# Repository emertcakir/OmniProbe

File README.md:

# OmniProbe

**A Universal Open-Source Debugging and Signal Analysis Platform for Embedded Engineers**

OmniProbe is an open-source hardware and firmware platform designed to simplify embedded system development, debugging, and protocol analysis.

Built around the RP2040 microcontroller, OmniProbe combines multiple engineering tools into a single compact device, reducing the need for separate adapters, analyzers, and interface boards.

---

## Why OmniProbe?

Embedded developers often rely on multiple tools for debugging and communication:

* SWD Debug Probe
* USB-to-UART Adapter
* Logic Analyzer
* SPI Debug Tool
* I2C Interface
* GPIO Test Board

OmniProbe aims to bring all of these capabilities into a single open-source platform.

---

## Key Features

### Debugging Interfaces

* SWD Debugging
* JTAG Support
* CMSIS-DAP Compatible Firmware

### Communication Interfaces

* USB to UART Bridge
* SPI Interface
* I2C Interface
* GPIO Access

### Logic Analyzer

* Up to 16 Digital Channels
* RP2040 PIO-Based Sampling Engine
* Planned Sigrok / PulseView Integration

### Multi-Voltage Operation

* 1.8V Support
* 3.3V Support
* 5V Support
* Bidirectional Level Shifting

### Hardware Features

* USB Type-C Connectivity
* ESD Protection
* Polyfuse Protection
* EMI Filtering
* Reverse Polarity Protection

---

## Hardware Architecture

The hardware architecture is divided into several independent modules:

* Power Management
* USB Type-C Interface
* RP2040 Core
* QSPI Flash Memory
* Level Shifting Subsystem
* Debug Interfaces
* Logic Analyzer Engine
* Protection Layer

This modular architecture allows future expansion without redesigning the entire system.

---

## Project Goals

* Open-Source Hardware
* Open-Source Firmware
* Professional Development Tool
* Affordable Manufacturing Cost
* Maker-Friendly Design
* Educational Value
* Extensible Architecture

---

## Repository Structure

```text
OmniProbe/
├── docs/
├── hardware/
├── firmware/
├── software/
├── tests/
└── assets/
```

---

## Current Status

Project Phase: System Architecture & Hardware Design

OmniProbe is currently in the hardware architecture and schematic design phase. The project is being developed as a fully open-source platform, including hardware design files, documentation, and firmware sources.

The first release focuses on establishing a reliable and extensible foundation for debugging, protocol analysis, and embedded development workflows.

Future updates will expand functionality, improve performance, and introduce additional protocol support while maintaining compatibility with the existing hardware platform.
---

## Open Hardware

All design files, schematics, PCB layouts, BOMs, and firmware sources will be publicly available.

The objective of OmniProbe is not only to provide a useful engineering tool, but also to serve as a learning resource for hardware and embedded system developers.

---

## Contributing

Contributions, design reviews, bug reports, feature requests, and pull requests are welcome.

---

## License

MIT License

---

## Disclaimer

OmniProbe is currently under active development. Hardware and firmware specifications may change before the first stable release.

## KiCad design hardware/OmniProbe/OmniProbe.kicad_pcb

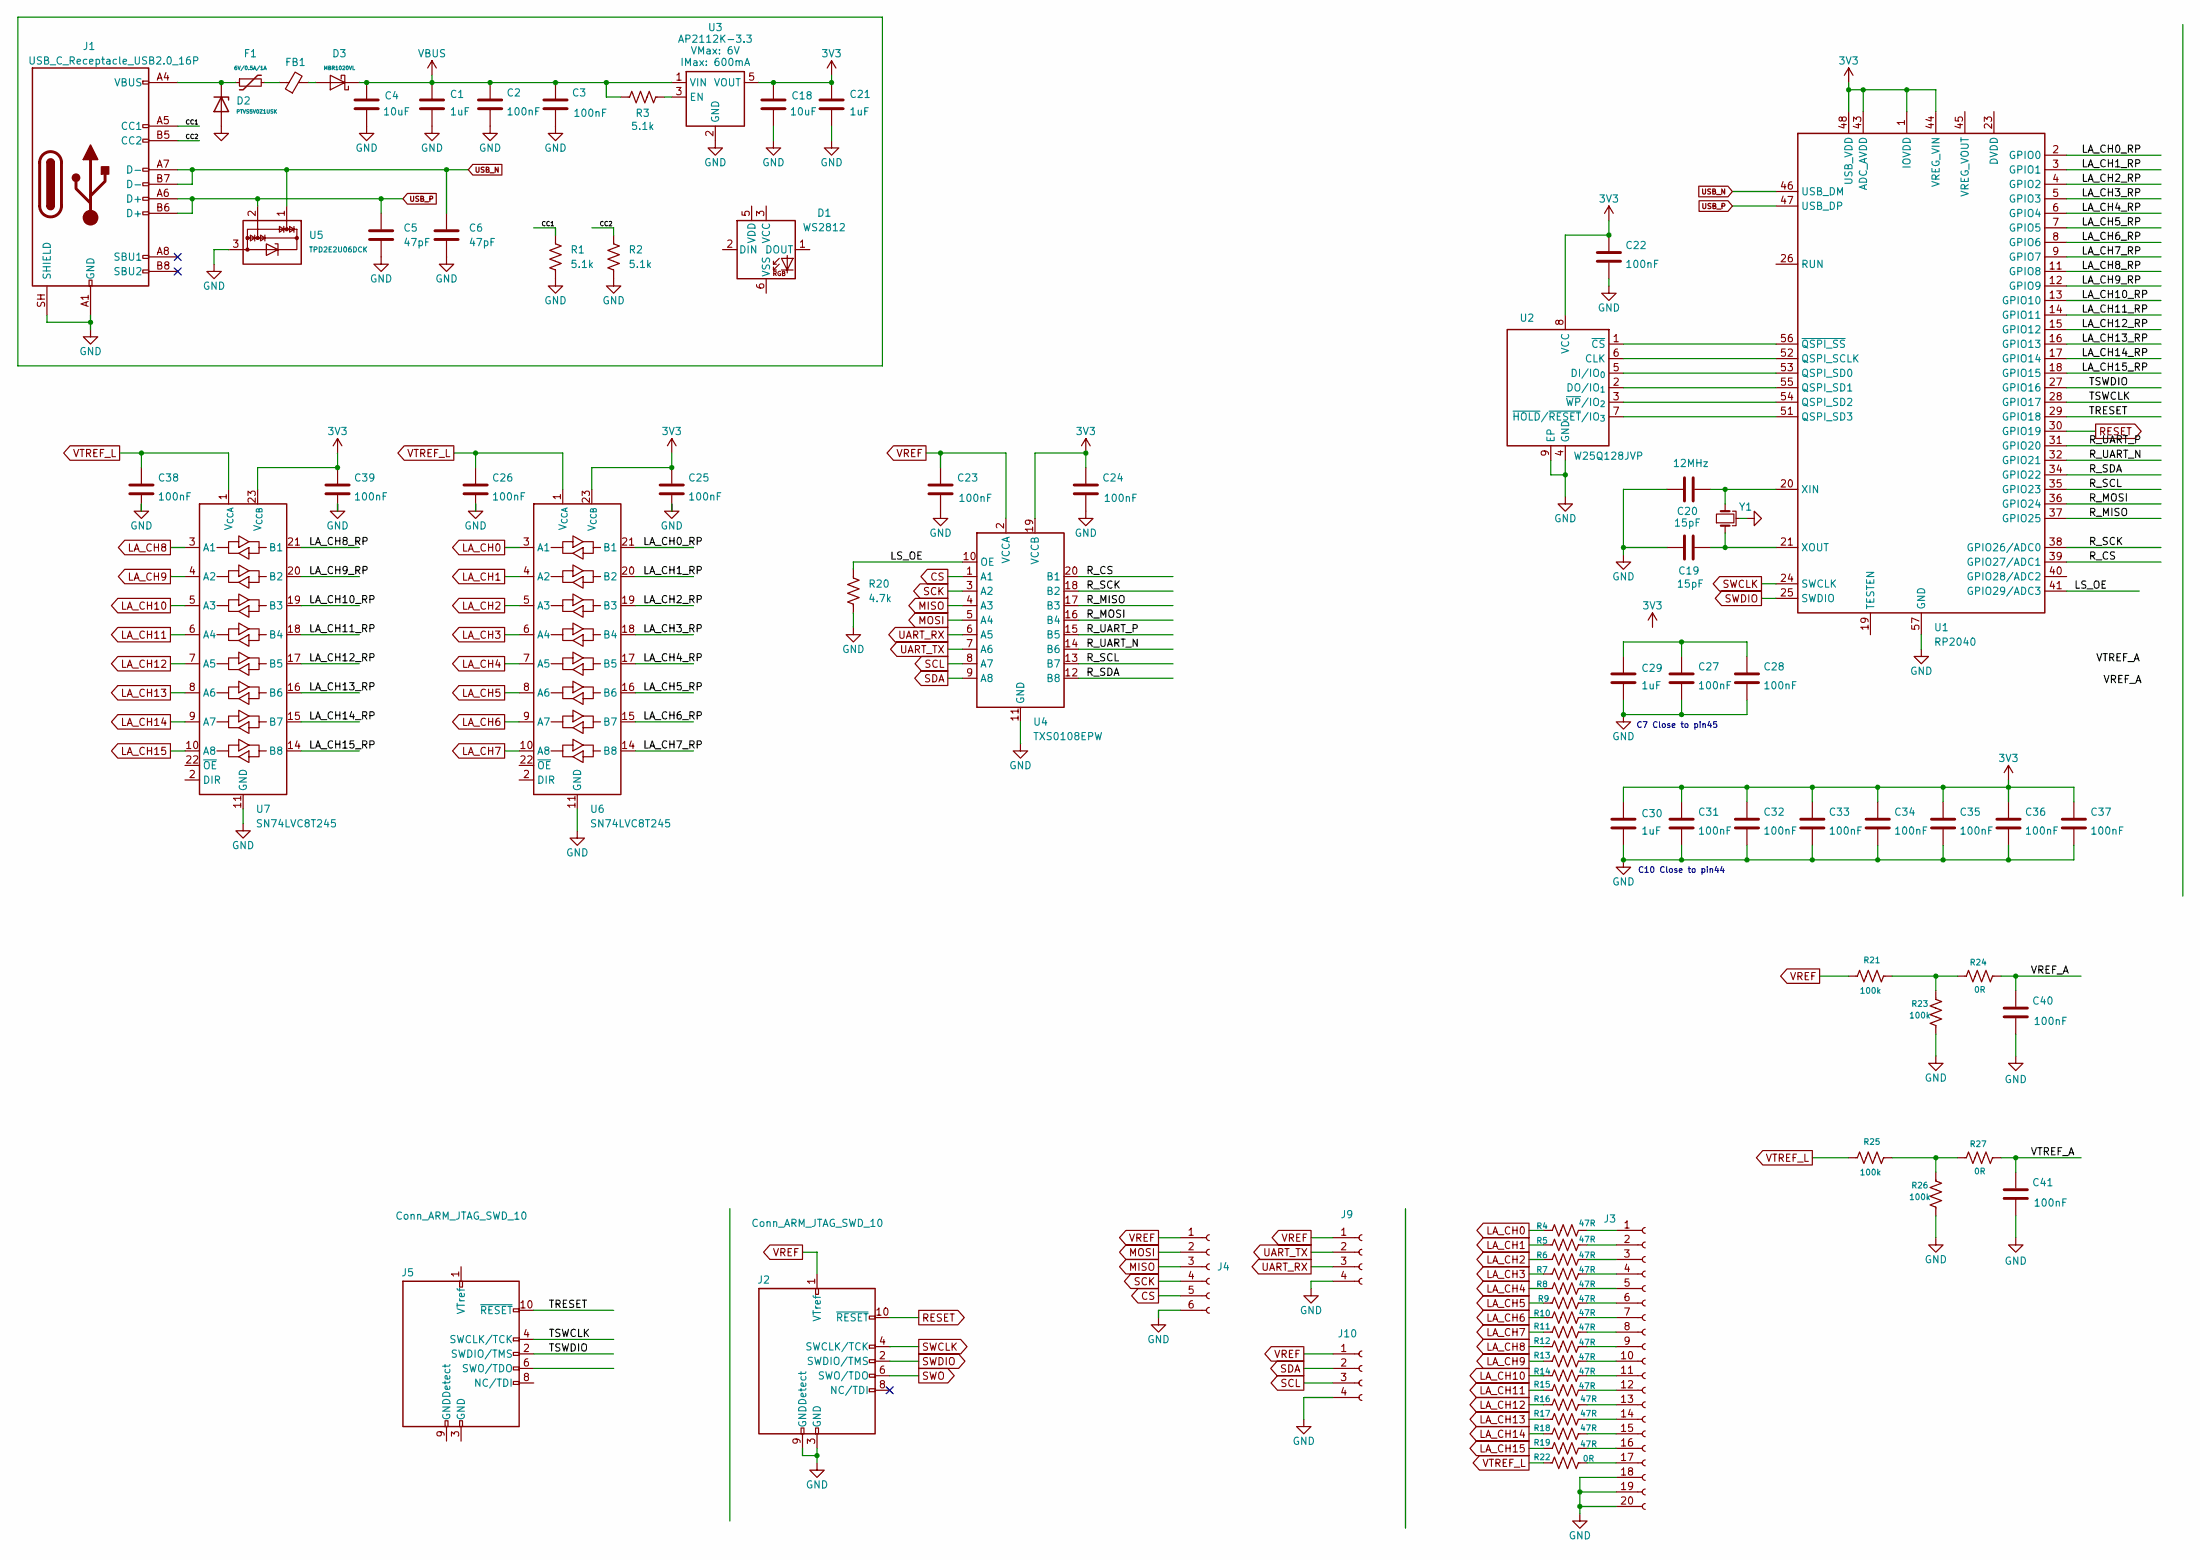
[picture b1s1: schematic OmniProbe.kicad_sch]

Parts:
C1, C21: 1uF; C_0603_1608Metric
C2, C3, C22, C23, C24, C25, C26, C38, C39, C40, C41: 100nF; C_0603_1608Metric
C4, C18: 10uF; C_0603_1608Metric
C5, C6: 47pF; C_0603_1608Metric
C19, C20: 15pF; C_0402_1005Metric
C27, C28, C31, C32, C33, C34, C35, C36, C37: 100nF; C_0402_1005Metric_Pad0.74x0.62mm_HandSolder
C29, C30: 1uF; C_0402_1005Metric_Pad0.74x0.62mm_HandSolder
D1: WS2812; LED_WS2812_PLCC6_5.0x5.0mm_P1.6mm
D2: PTVS5V0Z1USK; Nexperia_DSN1608-2_1.6x0.8mm
D3: MBR1020VL; D_SOD-123F
F1: 6V/0.5A/1A; 0805
FB1: FerriteBead_Small; L_0603_1608Metric
J1: USB_C_Receptacle_USB2.0_16P; USB_C_Receptacle_GCT_USB4105-xx-A_16P_TopMnt_Horizontal
J2, J5: Conn_ARM_JTAG_SWD_10; PinHeader_2x05_P1.27mm_Vertical
J3: Conn_01x20_Socket; PinHeader_1x20_P2.54mm_Vertical
J4: Conn_01x06_Socket; PinHeader_1x06_P2.54mm_Vertical
J9, J10: Conn_01x04_Socket; PinHeader_1x04_P2.54mm_Vertical
R1, R2, R3: 5.1k; R_0603_1608Metric
R4, R5, R6, R7, R8, R9, R10, R11, R12, R13, R14, R15, R16, R17, R18, R19: 47R; R_0603_1608Metric
R20: 4.7k; R_0603_1608Metric
R21, R23, R25, R26: 100k; R_0603_1608Metric
R22, R24, R27: 0R; R_0603_1608Metric
U1: RP2040; QFN-56-1EP_7x7mm_P0.4mm_EP3.2x3.2mm_ThermalVias
U2: W25Q128JVP; WSON-8-1EP_6x5mm_P1.27mm_EP3.4x4.3mm
U3: AP2112K-3.3; SOT23-5
U4: TXS0108EPW; TSSOP-20_4.4x6.5mm_P0.65mm
U5: TPD2E2U06DCK; SOT-323_SC-70
U6, U7: SN74LVC8T245; TSSOP-24_4.4x7.8mm_P0.65mm
Y1: 12MHz; Crystal_SMD_Abracon_ABM10-4Pin_2.5x2.0mm

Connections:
3V3: C18.1, C21.1, C22.1, C24.1, C25.1, C30.1, C31.1, C32.1, C33.1, C34.1, C35.1, C36.1, C37.1, C39.1, U1.1 (IOVDD), U1.10 (IOVDD), U1.22 (IOVDD), U1.33 (IOVDD), U1.42 (IOVDD), U1.43 (ADC_AVDD), U1.44 (VREG_VIN), U1.48 (USB_VDD), U1.49 (IOVDD), U2.8 (VCC), U3.5 (VOUT), U4.19 (VCCB), U6.23 (V_{CCB}), U6.24 (V_{CCB}), U7.23 (V_{CCB}), U7.24 (V_{CCB})
/CC1: J1.A5 (CC1), R1.1
/CC2: J1.B5 (CC2), R2.1
/LA_CH0_RP: U1.2 (GPIO0), U6.21 (B1)
/LA_CH1_RP: U1.3 (GPIO1), U6.20 (B2)
/LA_CH2_RP: U1.4 (GPIO2), U6.19 (B3)
/LA_CH3_RP: U1.5 (GPIO3), U6.18 (B4)
/LA_CH4_RP: U1.6 (GPIO4), U6.17 (B5)
/LA_CH5_RP: U1.7 (GPIO5), U6.16 (B6)
/LA_CH6_RP: U1.8 (GPIO6), U6.15 (B7)
/LA_CH7_RP: U1.9 (GPIO7), U6.14 (B8)
/LA_CH8_RP: U1.11 (GPIO8), U7.21 (B1)
/LA_CH9_RP: U1.12 (GPIO9), U7.20 (B2)
/LA_CH10_RP: U1.13 (GPIO10), U7.19 (B3)
/LA_CH11_RP: U1.14 (GPIO11), U7.18 (B4)
/LA_CH12_RP: U1.15 (GPIO12), U7.17 (B5)
/LA_CH13_RP: U1.16 (GPIO13), U7.16 (B6)
/LA_CH14_RP: U1.17 (GPIO14), U7.15 (B7)
/LA_CH15_RP: U1.18 (GPIO15), U7.14 (B8)
/LS_OE: R20.1, U1.41 (GPIO29/ADC3), U4.10 (OE)
/R_CS: U1.39 (GPIO27/ADC1), U4.20 (B1)
/R_MISO: U1.37 (GPIO25), U4.17 (B3)
/R_MOSI: U1.36 (GPIO24), U4.16 (B4)
/R_SCK: U1.38 (GPIO26/ADC0), U4.18 (B2)
/R_SCL: U1.35 (GPIO23), U4.13 (B7)
/R_SDA: U1.34 (GPIO22), U4.12 (B8)
/R_UART_N: U1.32 (GPIO21), U4.14 (B6)
/R_UART_P: U1.31 (GPIO20), U4.15 (B5)
/TRESET: J5.10 (~RESET), U1.29 (GPIO18)
/TSWCLK: J5.4 (SWCLK/TCK), U1.28 (GPIO17)
/TSWDIO: J5.2 (SWDIO/TMS), U1.27 (GPIO16)
/VREF_A: C40.1, R24.2
/VTREF_A: C41.1, R27.2
CS: J4.5, U4.1 (A1)
GND: C1.2, C2.2, C3.2, C4.2, C5.2, C6.2, C18.2, C19.1, C20.1, C21.2, C22.2, C23.2, C24.2, C25.2, C26.2, C27.2, C28.2, C29.2, C30.2, C31.2, C32.2, C33.2, C34.2, C35.2, C36.2, C37.2, C38.2, C39.2, C40.2, C41.2, D2.2 (A), J1.A1 (GND), J1.A12 (GND), J1.B1 (GND), J1.B12 (GND), J1.SH (SHIELD), J2.3 (GND), J2.5 (GND), J2.9 (GNDDetect), J3.18, J3.19, J3.20, J4.6, J9.4, J10.4, R1.2, R2.2, R20.2, R23.1, R26.1, U1.57 (GND), U2.4 (GND), U2.9 (EP), U3.2 (GND), U4.11 (GND), U5.3, U6.11 (GND), U6.12 (GND), U6.13 (GND), U7.11 (GND), U7.12 (GND), U7.13 (GND), Y1.2, Y1.4
LA_CH0: R4.1, U6.3 (A1)
LA_CH1: R5.1, U6.4 (A2)
LA_CH2: R6.1, U6.5 (A3)
LA_CH3: R7.1, U6.6 (A4)
LA_CH4: R8.1, U6.7 (A5)
LA_CH5: R9.1, U6.8 (A6)
LA_CH6: R10.1, U6.9 (A7)
LA_CH7: R11.1, U6.10 (A8)
LA_CH8: R12.1, U7.3 (A1)
LA_CH9: R13.1, U7.4 (A2)
LA_CH10: R14.1, U7.5 (A3)
LA_CH11: R15.1, U7.6 (A4)
LA_CH12: R16.1, U7.7 (A5)
LA_CH13: R17.1, U7.8 (A6)
LA_CH14: R18.1, U7.9 (A7)
LA_CH15: R19.1, U7.10 (A8)
MISO: J4.3, U4.4 (A3)
MOSI: J4.2, U4.5 (A4)
unnamed: C27.1, C28.1, C29.1
unnamed: D2.1 (K), F1.1, J1.A4 (VBUS), J1.A9 (VBUS), J1.B4 (VBUS), J1.B9 (VBUS)
unnamed: D3.2 (A), FB1.2
unnamed: F1.2, FB1.1
unnamed: J3.1, R4.2
unnamed: J3.2, R5.2
unnamed: J3.3, R6.2
unnamed: J3.4, R7.2
unnamed: J3.5, R8.2
unnamed: J3.6, R9.2
unnamed: J3.7, R10.2
unnamed: J3.8, R11.2
unnamed: J3.9, R12.2
unnamed: J3.10, R13.2
unnamed: J3.11, R14.2
unnamed: J3.12, R15.2
unnamed: J3.13, R16.2
unnamed: J3.14, R17.2
unnamed: J3.15, R18.2
unnamed: J3.16, R19.2
unnamed: J3.17, R22.2
unnamed: J5.3 (GND), J5.5 (GND)
unnamed: R21.2, R23.2, R24.1
unnamed: R25.2, R26.2, R27.1
unnamed: U1.23 (DVDD), U1.50 (DVDD)
unnamed: U1.52 (QSPI_SCLK), U2.6 (CLK)
unnamed: U1.53 (QSPI_SD0), U2.5 (DI/IO_{0})
unnamed: U1.55 (QSPI_SD1), U2.2 (DO/IO_{1})
unnamed: U1.54 (QSPI_SD2), U2.3 (~WP/IO_{2})
unnamed: U1.51 (QSPI_SD3), U2.7 (~HOLD/~RESET/IO_{3})
unnamed: C20.2, U1.20 (XIN), Y1.3
unnamed: C19.2, U1.21 (XOUT), Y1.1
unnamed: U1.56 (~QSPI_SS), U2.1 (~CS)
unnamed: R3.2, U3.3 (EN)
RESET: J2.10 (~RESET), U1.30 (GPIO19)
SCK: J4.4, U4.3 (A2)
SCL: J10.3, U4.8 (A7)
SDA: J10.2, U4.9 (A8)
SWCLK: J2.4 (SWCLK/TCK), U1.24 (SWCLK)
SWDIO: J2.2 (SWDIO/TMS), U1.25 (SWDIO)
SWO: J2.6 (SWO/TDO)
UART_RX: J9.3, U4.6 (A5)
UART_TX: J9.2, U4.7 (A6)
USB_N: C6.1, J1.A7 (D-), J1.B7 (D-), U1.46 (USB_DM), U5.1
USB_P: C5.1, J1.A6 (D+), J1.B6 (D+), U1.47 (USB_DP), U5.2
VBUS: C1.1, C2.1, C3.1, C4.1, D3.1 (K), R3.1, U3.1 (VIN)
VREF: C23.1, J2.1 (VTref), J4.1, J9.1, J10.1, R21.1, U4.2 (VCCA)
VTREF_L: C26.1, C38.1, R22.1, R25.1, U6.1 (V_{CCA}), U7.1 (V_{CCA})

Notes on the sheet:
C7 Close to pin45
C10 Close to pin44

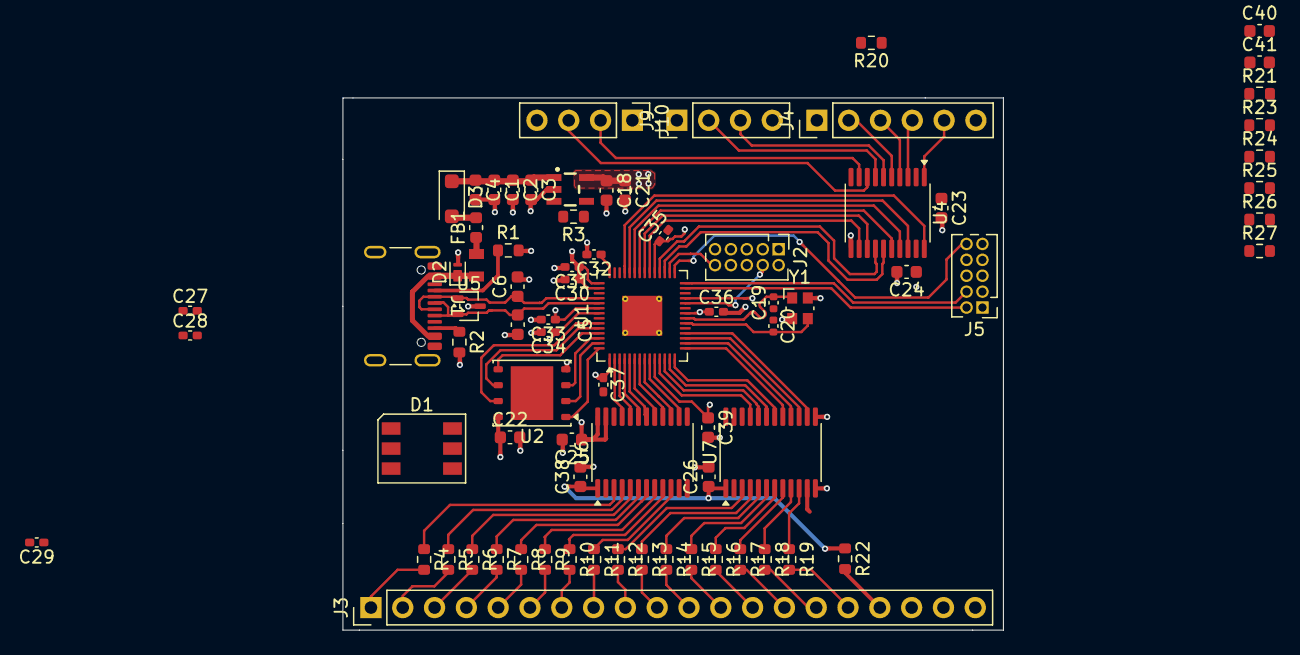
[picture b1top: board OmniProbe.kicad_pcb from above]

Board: 4 copper layers, 52.7 x 42.5 mm, 77 parts (0 on the bottom side), 100 nets.

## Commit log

2026-06-15 v0.1
2026-06-28 V0.11
